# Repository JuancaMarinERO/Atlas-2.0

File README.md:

# Atlas-2.0

Atlas 2.0 es un proyecto de dron autónomo diseñado para aplicar herbicida casero y controlar la especie invasora Thunbergia alata en zonas rurales.
🔧 Consulta la Wiki del repositorio para más detalles sobre el diseño, componentes, pruebas y documentación técnica.

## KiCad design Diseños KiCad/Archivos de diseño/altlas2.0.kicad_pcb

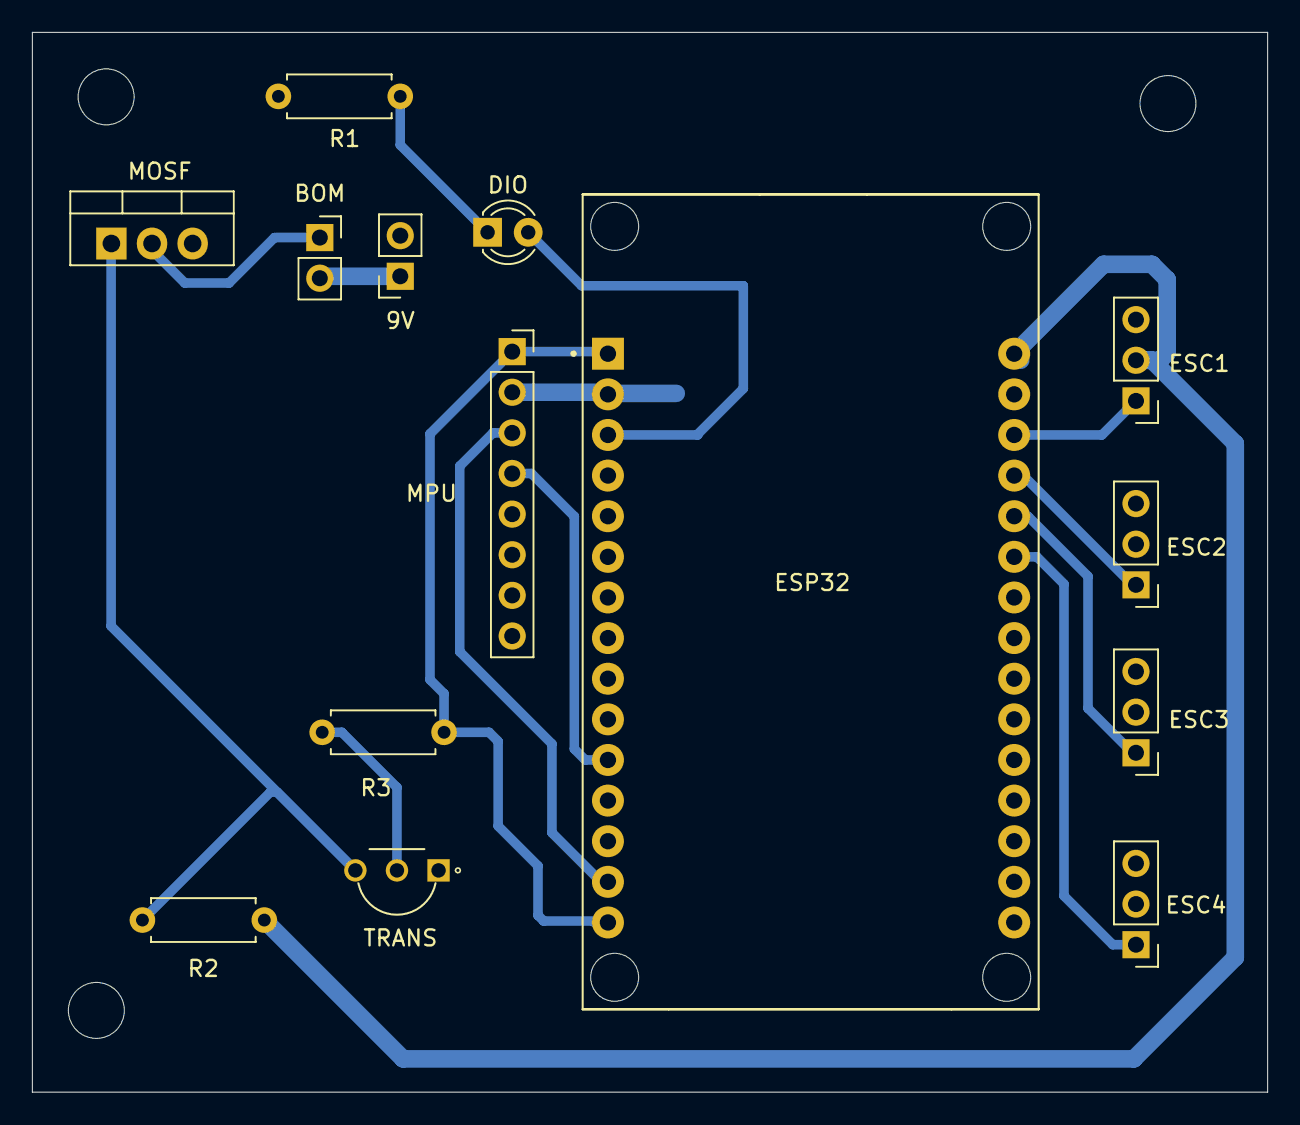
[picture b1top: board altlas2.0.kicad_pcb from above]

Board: 2 copper layers, 77.2 x 66.3 mm, 14 parts (0 on the bottom side), 15 nets.

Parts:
9V: Bateria 9V; PinSocket_1x02_P2.54mm_Vertical
BOM: Mini bomba; PinSocket_1x02_P2.54mm_Vertical
DIO: LED; LED_D3.0mm_IRGrey
ESC1: ESC 1; PinHeader_1x03_P2.54mm_Vertical
ESC2: ESC 2; PinHeader_1x03_P2.54mm_Vertical
ESC3: ESC 3; PinHeader_1x03_P2.54mm_Vertical
ESC4: ESC 4; PinHeader_1x03_P2.54mm_Vertical
ESP32: ESP32-DEVKIT-V1; MODULE_ESP32_DEVKIT_V1
MOSF: IRLZ44N; TO-220-3_Vertical
MPU: MPU-6050; PinSocket_1x08_P2.54mm_Vertical
R1, R2, R3: R_US; R_Axial_DIN0207_L6.3mm_D2.5mm_P7.62mm_Horizontal
TRANS: LP395Z_NOPB; TO-92

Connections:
+5V: ESC1.2, ESP32.30 (VIN), R2.1
+9V: 9V.1, BOM.2
GND: 9V.2, ESC1.3, ESC2.3, ESC3.3, ESC4.3, ESP32.2 (GND), ESP32.29 (GND), MOSF.3 (S), MPU.2, R1.1, TRANS.1
unnamed: DIO.2 (A), ESP32.3 (D15)
unnamed: DIO.1 (K), R1.2
unnamed: ESC1.1, ESP32.28 (D13)
unnamed: ESC2.1, ESP32.27 (D12)
unnamed: ESC3.1, ESP32.26 (D14)
unnamed: ESC4.1, ESP32.25 (D27)
unnamed: ESP32.1 (3V3), ESP32.15 (D23), MPU.1, R3.1
unnamed: ESP32.14 (D22), MPU.3
unnamed: ESP32.11 (D21), MPU.4
unnamed: BOM.1, MOSF.2 (D)
unnamed: MOSF.1 (G), R2.2, TRANS.3
unnamed: R3.2, TRANS.2

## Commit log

2025-07-23 Archivos refrentes al proyecto
2025-07-23 Create Aplicación Movil
2025-07-23 Create hola
2025-07-23 Actualización de archivos
    Se suben los archivos referentes al proyecto
